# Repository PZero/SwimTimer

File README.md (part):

# SwimTimer

Automatic lap times in the pool: a tag under the swim cap and a poolside display detect start and finish, with no buttons.

Updated on **2026-11-12**. Single public repository `PZero/SwimTimer`: XIAO test tags and their firmware, tools page (GitHub Pages: https://pzero.github.io/SwimTimer/), online collaboration app (Firebase, Italian and English: https://swimtimer-pzero.web.app, with contact form and poolside display demo), ESP32 prototype, nRF52840 tag (KiCad, Gerber, JLCPCB and NextPCB files), programmer HAT, technical wallpapers and three videos (first pool test, progress update and first presentation).

> **Language.** This README is in English. Internal working documents in [`docs/`](docs/) (state, decisions, requirements, design) are written in Italian.

### Houston, we have a problem (3 minutes, latest)

Watch the English version on YouTube: **https://youtu.be/mj6OTWkjgwk**. Italian version: https://youtu.be/85RNvPnFV1E.

The tag stopped in the pool on 11 November 2026: a "black box" diagnosis after every connection showed that the Bluetooth task's stack was too small. The video shows the three changes (black box, bigger stack, poolside station that confirms every block only after saving and reading it back: almost 1,000 blocks on the bench, zero lost) and the stroke-rhythm idea for timing the finish, a promising lead still being checked. Animations drawn in code with made-up data. Sources in [`media/video/`](media/video/) (`genera_video_v4.py`, `musica_v4.py`, `STORYBOARD_v4.md`); the video files are not in the repository.

### The first pool test (2.5 minutes)

Watch the English version on YouTube: **https://youtu.be/bs7WDUuwb-A**. Italian version: https://youtu.be/J01CR2nldp8.

The first real pool test (9 November 2026): IMU filters on the raw data, why the hand-made labels were not precise enough, OpenCV on the underwater video as the new reference, and the decision for a structured method with a small neural network only for the finish. Real images and data from the author's own session (author's choice). Sources in [`media/video/`](media/video/) (`genera_video_v3.py`, `musica_v3.py`); the video files and thumbnails are not in the repository.

### Progress update video (2 minutes)

Watch the English version on YouTube: **https://youtu.be/JLs5JJG4JG8**. Italian version: https://youtu.be/_Htx2DawnF8.

A progress update on the project as of 2026-11-08. The soundtrack is original music generated by code. Sources in [`media/video/`](media/video/); the video files are not in the repository.

### First presentation (2 minutes)

English: **https://youtu.be/EVrdSybpnE4**. Italian: https://youtu.be/_2UzpOqblVI.

## Table of contents
- [What is SwimTimer](#what-is-swimtimer)
- [Current status](#current-status)
- [Test methodology: raw data, video and hand annotation](#test-methodology-raw-data-video-and-hand-annotation)
- [System architecture](#system-architecture)
- [ESP32 prototype, firmware 0.4.3](#esp32-prototype-firmware-043)
- [nRF52840 tag](#nrf52840-tag)
- [XIAO nRF52840 Sense test tags](#xiao-nrf52840-sense-test-tags)
- [Tag to display synchronization](#tag-to-display-synchronization)
- [USB receiver and host (bench results)](#usb-receiver-and-host-bench-results)
- [Base station (Raspberry Pi 3)](#base-station-raspberry-pi-3)
- [Tools page (`tools/index.html`)](#tools-page-toolsindexhtml)
- [Analysis: video (OpenCV) and IMU test bench](#analysis-video-opencv-and-imu-test-bench)
- [Online collaboration app](#online-collaboration-app)
- [External reviews](#external-reviews-v04)
- [Programmer HAT for Raspberry Pi 3/4](#programmer-hat-for-raspberry-pi-34)
- [Poolside display mockup and proposed architecture](#poolside-display-mockup-and-proposed-architecture)
- [Planned features and ideas](#planned-features-and-ideas)
- [Technical wallpaper gallery](#technical-wallpaper-gallery)
- [Repository structure](#repository-structure)
- [How to regenerate the files](#how-to-regenerate-the-files)
- [Ordering flow: JLCPCB and NextPCB](#ordering-flow-jlcpcb-and-nextpcb)
- [Roadmap and open issues](#roadmap-and-open-issues)
- [Privacy and security](#privacy-and-security)
- [License and author](#license-and-author)

## What is SwimTimer

**Problem.** In the pool, lap times and rests get lost. Looking at a watch or pressing a button interrupts the workout.

**Solution.** A small tag with an inertial sensor (accelerometer and gyroscope) is worn under the swim cap. It detects the wall push-off (start), the turns and the stillness at the finish on its own. A poolside display shows the times.

**Physical constraint.** 2.4 GHz BLE does not travel through water. Time is not measured with the radio signal: the sensor on the tag decides. BLE is used only out of the water, to detect proximity to the display and to transfer data. Full feasibility analysis: [`docs/IDEA.md`](docs/IDEA.md) (in Italian).

## Current status

| Area | Status |
|---|---|
| ESP32-S3 + BMI160 prototype, firmware **0.4.3** | Working on the bench; no pool tests yet. Its tools were removed from the tools page on 2026-11-08 |
| LilyGO T-RGB display (4-hand pace clock) | Board works, **screen broken** (torn ribbon cable). Replacement 2.8″ screen to order. Used now without a screen (see the display firmware row) |
| nRF52840 tag **v0.5 "economy"** | Ready: 21.59 x 28.0 mm, 2 layers, DRC 0, ERC 0 errors, `verifica_v05.py` 100/100 pins. JLCPCB files plus NextPCB files (single board and 3x1 / 2x1 panels); JLC placement preview checked, Q1 and U6 rotations fixed (commit `dea9744`) |
| nRF52840 tag **v0.6 "Rev0"** (new) | 4 layers 0.8 mm, 21.59 x 28.5 mm, no BGA (NextPCB Rev0 rejects pitch below 0.45 mm). Files generated; JLC rotations of the new SOT-23 parts still to verify in a JLC preview |
| XIAO nRF52840 Sense test tags | One board in use on the bench ([`hardware/xiao/README.md`](hardware/xiao/README.md)). Firmware 0.5.2 (no automatic sleep on USB power), 0.5.3 (USB during a recording closes it and restarts in normal mode) and 0.5.4 (charge current 100 mA) flashed and checked on the bench; test cell 1000 mAh; pool recording download and recorded data not yet checked; not yet used in the pool |
| XIAO firmware **0.6.1** (`firmware/xiao-stream`, test build on both tags) | Automatic resume after a crash or watchdog reset (max 3 in a row), 8 s watchdog, fault context and persistent diary, IMU FIFO realignment with content check, continuous session time (start-up 500 ms), no idle without USB, USB rules, standby command from the display. Standby from the page, rest stop and idle on the charger **not yet verified**. The published OTA release is still 0.5.4 |
| Tag firmware **0.6.3** (`firmware/xiao-stream`) | 238-byte fragments (READY v2), notification queue, 2M PHY / DLE, DIAGNOSIS message after every connection, 4-aligned flash reads, BLE stack 8 KB. **0.6.4** (stack 10 KB, stays connected while recording, DIAGNOSIS2; written 2026-11-12, 60-minute bench run pending) |
| Receiver firmware **0.1.6** (`firmware/ricevitore`) + host `stazione/ricevitore_host.py` | XIAO nRF52840 Sense on USB, central for 2 tags; the host saves, fsyncs and re-reads each block before the OK. Bench: 1 tag ~16.5 KB/s, 2 tags ~17.6 KB/s total, 0 blocks lost. Receiver **0.1.7** written (DIAGNOSIS2 relay). Runs as a service on the Raspberry Pi 3 (2 tags downloaded, 0 blocks discarded); not yet tested in the pool |
| Display firmware `firmware/display-sync` | LilyGO T-RGB without a working screen: receives the blocks from up to 3 tags, verifies, writes to microSD and confirms. Creates the Wi-Fi network «SwimTimer» with a status page for iPhone (`http://192.168.4.1`), which also shows warnings, the recording button and the standby button for the tags. Dry run (0.6.0): 2 tags x 15 min, 666 blocks saved and confirmed, 0 CRC errors, 0 anomalies. Signal strength still to be tuned |
| Display enclosure `hardware/display-involucro/` | Parametric OpenSCAD design: PLA vase, silicone cap, fork with a 15° detent swivel; STL files and renders. Fit on the real board still to be checked |
| Tools page `tools/index.html` | XIAO only: Live, Recording, Annotation and Firmware tabs, USB / Bluetooth / Demo. Also published on the Firebase site at `/strumenti/`, with an "Upload online" button. Tested in the browser with Demo and simulated ports, not yet with the real XIAO over USB for a full download |
| Online collaboration app | Bilingual (IT/EN) public landing page with a contact form, and members' area (Google login, admin approval of new accounts, admin page for messages). Poolside display section with a live demo. Firestore rules tested with 17 emulator tests. Not yet used with real sessions |
| Test campaign 1 | **Planned**: one swimmer (the author), 50 m pool, wall drills, then a real training session as verification. See [Test methodology](#test-methodology-raw-data-video-and-hand-annotation) |
| Order | **Not placed yet**: preview, finish choice (HASL/ENIG), DFM ticket and cost decision pending |
| nRF52840 tag firmware | To be written (Zephyr / nRF Connect SDK) |
| Programmer HAT for Raspberry Pi 3/4 | Designed, regenerated on v0.5 (TP1-TP7 unchanged), DRC 0; **not built yet** |

## Test methodology: raw data, video and hand annotation

The core of SwimTimer is a set of **filters** that recognise strokes, breaths, turns, starts and finishes from the IMU of a tag worn under the cap. Before writing those filters we need **ground truth**: real swimming data in which every event is known. For this phase the tag is a **Seeed XIAO nRF52840 Sense** (same SoC as the custom board, which is still being manufactured) running the pool recording firmware [`firmware/xiao-stream`](firmware/xiao-stream/) 0.5.x.

**Test campaign 1 (planned).** The first campaign has a deliberately small scope:

- **One swimmer only**: the author of the project. No other person is recorded.
- **Pool**: 50 m, with a wall for the drills.
- **Drills at one wall** (turns, starts, finishes), repeated to collect many examples of each event with known timing.
- **Real training** afterwards, used to verify the filters on a session that was not used to tune them.
- **Video** from an iPhone and an Insta360 camera, both at 30 fps for now (the page does not yet handle 25 fps).
- **Annotation by hand first**, in the *Annotation* tab. Filters are developed and compared **only in the web page**, after the whole session is annotated.

The steps below describe the procedure of each session.

1. **Record raw data in the pool.** The swimmer wakes the tag (2 taps, blue LED, 2 taps): it records the raw accelerometer and gyroscope at 208 Hz to its flash, with BLE off (BLE does not cross water). The swimmer is filmed from the deck with a phone (H.264, 30 fps).
2. **Sync gesture.** With the tag under the cap, the swimmer gives **5 large, clearly visible taps** on it. The taps are sharp peaks in the data and visible frames in the video: the **5th tap** is the common reference point.
3. **Swim 5-10 minutes,** then put the tag in the bag: after 180 s of rest it closes the recording and sleeps. The data survives even if the battery runs out on the way home.
4. **Download at home over USB** from the *Recording* tab of [`tools/index.html`](tools/index.html) (Web Serial) or with [`scarica.py`](firmware/xiao-stream/scarica.py): a `.swr` file.
5. **Align video and data** in the *Annotation* tab: press **X** on the video frame of the 5th tap and click the 5th peak in the zoomable raw-data chart. The page computes the offset; from then on the data follow the video, forwards and backwards.
6. **Annotate events by hand** while watching the video (slow motion, frame by frame): **B** stroke (hand entry), **R** breath (mouth out of the water), **V** turn start, **F** turn end, **P** start, **A** arrival. Events are stored in video time, so a later offset correction moves them all at once; they are saved as a project JSON and a CSV.
7. **Develop the filters** on the raw data, re-process the same recording and **compare** the automatic events with the hand-annotated ones (matches within a time tolerance, precision, recall, timing error). This happens only after the whole session has been annotated.

Recordings, videos and annotation projects are health data: they stay on the PC and are excluded from git; the repository only contains code and invented test data.

## System architecture

```mermaid
flowchart LR
  subgraph TAG[Tag under the swim cap]
    IMU[6-axis IMU] -- SPI --> MCU[nRF52840 / ESP32-S3<br/>BLE]
    FL[Flash] -- SPI --> MCU
    CEL[LiPo cell] --> MCU
  end
  MCU -- "BLE advertising (out of the water)" --> DSP[Poolside display<br/>LilyGO T-RGB 2.8 inch]
  MCU -- "GATT / OTA (out of the water)" --> WEB[Analysis page<br/>Web Bluetooth]
  MCU -. "flash recording,<br/>downloaded later" .-> WEB
  WEB -. "downloaded .swr files" .-> PCU[Member's browser]
  PCU -. "upload in chunks, annotations" .-> APP[Online collaboration app<br/>Firebase Spark, Firestore]
  DSP -- "pace clock, times" --> SWI[Swimmer]
  CHG[Charging base / programmer] -- "contacts under the tag" --> TAG
```

### Target poolside chain (decided 2026-11-12)

```text
Tag (XIAO nRF52840, under the cap)
   |  BLE, out of the water (encrypted sync protocol)
   v
Receiver (XIAO nRF52840 Sense, USB; firmware/ricevitore)
   |  USB serial, CRC frames
   v
Host (stazione/ricevitore_host.py, --stato JSON) on Raspberry Pi 3 (Raspberry Pi OS Lite 64-bit, headless)
   |  pannello.py (HTTP :8080) + pannello.html, kiosk browser on HDMI
   v
Portable 15.6" HDMI monitor (poolside display)
```

The receiver, the host and the Raspberry Pi station (systemd services, status panel, kiosk) are implemented; the Pi boots straight into the panel. See [USB receiver and host](#usb-receiver-and-host-bench-results).

Tests run with two tags streaming raw data; in normal operation only events (start, turns, stop) are exchanged. The LilyGO T-RGB display remains a test device for synchronization.

- **Synchronization.** After the swim the tag pushes its recorded blocks to the poolside display over BLE; the display verifies, stores and confirms them. See [Tag to display synchronization](#tag-to-display-synchronization).
- **Tag.** Under the cap, pressed against the skull. It decides START, turns and STOP on its own using the IMU and logs raw data to flash.
- **Poolside display.** Receives the tag's BLE advertisements without connecting. Shows a 4-hand pace clock. Goes to sleep after 5 minutes without a tag.
- **Tools page.** [`tools/index.html`](tools/index.html) connects to the XIAO over USB or Bluetooth, downloads and annotates recordings and updates the firmware. Details in [Tools page](#tools-page-toolsindexhtml).
- **Online app.** Optional collaboration area for sessions, video links and annotations. Details in [Online collaboration app](#online-collaboration-app).
- **BLE out of the water.** Underwater the signal disappears within a few centimetres: during the swim the tag works alone and hands over its data when the swimmer emerges or at the end of the session.

## ESP32 prototype, firmware 0.4.3

The prototype was used to tune the algorithms before the XIAO and custom boards. Since 2026-11-08 the tools page no longer supports it.

**Tag (prototype).** ESP32-S3 SuperMini + BMI160 (GY-BMI160), LiPo with main switch. Bill of materials: [`hardware/bom.md`](hardware/bom.md). Wiring: [`hardware/schema.md`](hardware/schema.md) (both in Italian).

**Firmware 0.4.3** (`firmware/test-collegamenti`, arduino-cli, core `esp32:esp32` 3.3.12):
- +/-16 g and 100 Hz, set with the sensors on and read back (up to 5 attempts);
- flash with two program copies and about 1.9 MB of LittleFS (about 40 minutes at 50 Hz);
- double tap = start recording, triple tap = stop (software detection, unreliable: about 1 in 10);
- BLE with data, status, commands, OTA and version; the same commands over USB; Bluetooth update with automatic rollback to the previous version;
- automatic I2C bus recovery, RGB LED feedback, last reset reason, voltage dividers on GPIO 1 (battery) and GPIO 2 (5V pin).

**Display** (`firmware/display-prova`): LilyGO T-RGB 2.8 inch, PlatformIO with espressif32 6.9.0, driver copied and adapted in `src/trgb/` (MIT license, Xinyuan-LilyGO).

**Build and upload the tag firmware:**
```
arduino-cli compile --fqbn esp32:esp32:esp32s3:CDCOnBoot=cdc --upload -p <COM> firmware/test-collegamenti
```

Related documents (in Italian): [`docs/RICERCA-ALGORITMI.md`](docs/RICERCA-ALGORITMI.md) (algorithm research), [`docs/LEZIONI-APPRESE.md`](docs/LEZIONI-APPRESE.md) (13 prototype lessons for the miniaturised board), [`docs/REQUISITI.md`](docs/REQUISITI.md) (requirements), [`docs/DESIGN.md`](docs/DESIGN.md) (design).

## nRF52840 tag

**Goal.** Replace the prototype with a miniature tag for the swim cap, assembled by the fab, with contact charging and programming through pads on the underside. Design document: [`hardware/nrf52840/progetto.md`](hardware/nrf52840/progetto.md) (Italian).

### Version history

| Version | Date | Board | Content | Outcome |
|---|---|---|---|---|
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
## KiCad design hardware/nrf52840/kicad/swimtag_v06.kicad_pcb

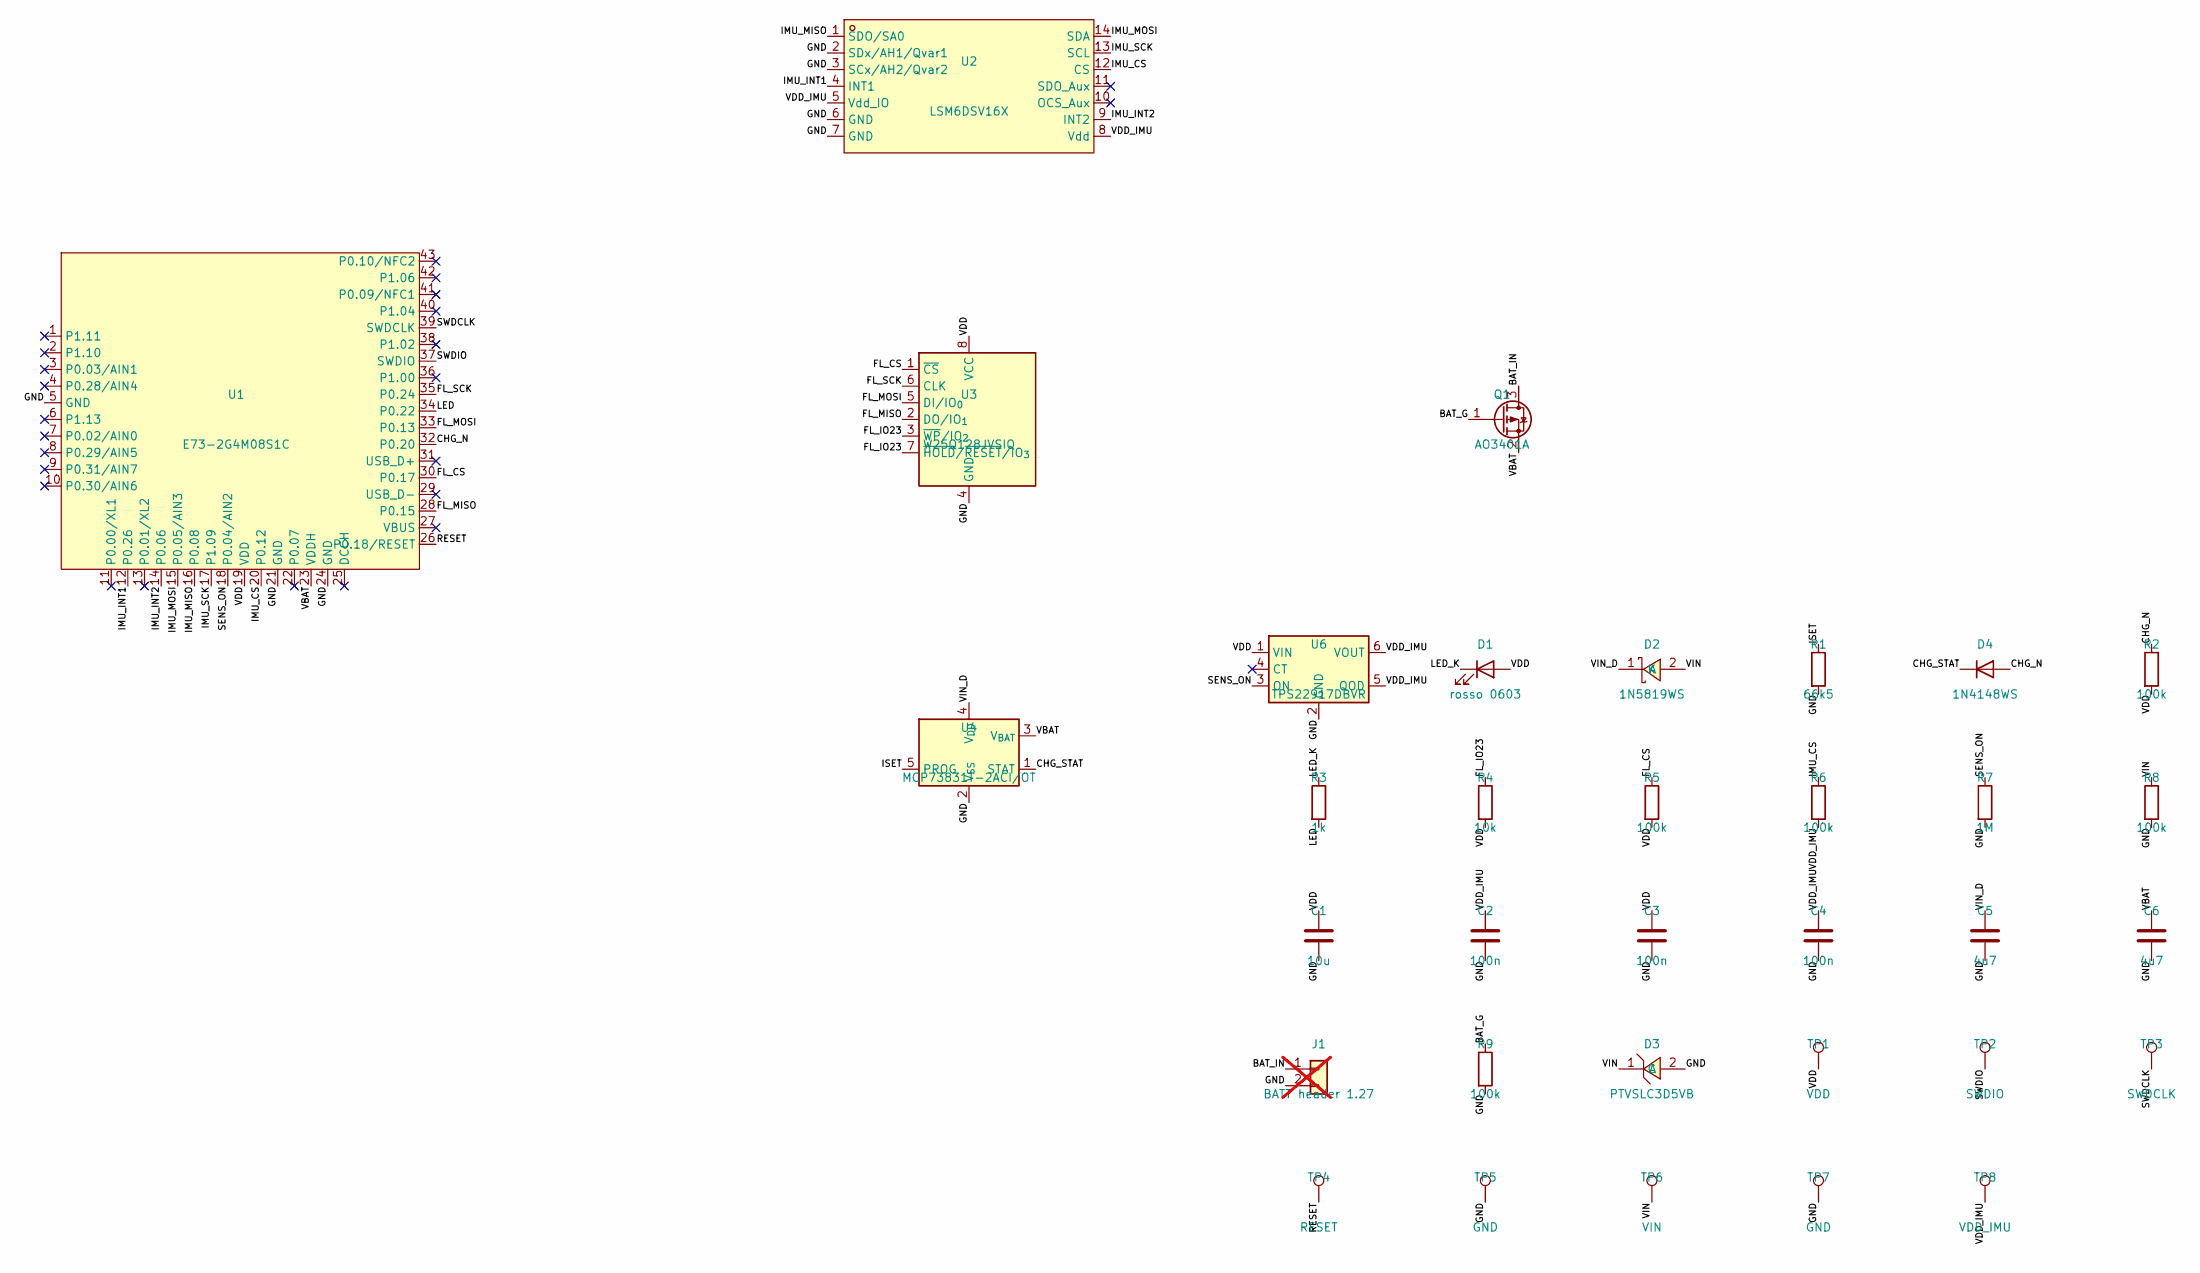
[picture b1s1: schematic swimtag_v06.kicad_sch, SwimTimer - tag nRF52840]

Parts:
C1: 10u; C_0402_1005Metric; LCSC C15525
C2, C3, C4: 100n; C_0402_1005Metric; LCSC C1525
C5, C6: 4u7; C_0402_1005Metric; LCSC C23733
D1: rosso 0603; LED_0603_1608Metric; LCSC C2286
D2: 1N5819WS; SOD-323_L1.8-W1.3-LS2.5-RD; LCSC C191023
D3: PTVSLC3D5VB; SOD-323_L1.8-W1.3-LS2.5-RD; LCSC C41408025
D4: 1N4148WS; SOD-323_L1.8-W1.3-LS2.5-RD; LCSC C2128
J1: BATT header 1.27; HDR-SMD_2P-P1.27-V-M-LS4.2-R1; LCSC C55213900; not fitted
Q1: AO3401A; SOT-23; LCSC C15127
R1: 66k5; R_0402_1005Metric; LCSC C172114
R2, R5, R6, R8, R9: 100k; R_0402_1005Metric; LCSC C25741
R3: 1k; R_0402_1005Metric; LCSC C11702
R4: 10k; R_0402_1005Metric; LCSC C25744
R7: 1M; R_0402_1005Metric; LCSC C26083
TP1: VDD; TestPoint_Pad_D2.0mm_NoCY
TP2: SWDIO; TestPoint_Pad_D2.0mm_NoCY
TP3: SWDCLK; TestPoint_Pad_D2.0mm_NoCY
TP4: RESET; TestPoint_Pad_D2.0mm_NoCY
TP5: GND; TestPoint_Pad_D2.0mm_NoCY
TP6: VIN; TestPoint_Pad_D2.5mm
TP7: GND; TestPoint_Pad_D2.5mm
TP8: VDD_IMU; TestPoint_Pad_D0.8mm
U1: E73-2G4M08S1C; WIRELM-SMD_E73-2G4M08S1C; LCSC C356849
U2: LSM6DSV16X; LGA-14_L3.0-W2.5-P0.50-BR; LCSC C5267406
U3: W25Q128JVSIQ; SOIC-8_5.3x5.3mm_P1.27mm; LCSC C97521
U4: MCP73831T-2ACI/OT; SOT-23-5; LCSC C424093
U6: TPS22917DBVR; SOT-23-6; LCSC C2681320

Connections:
/BAT_G: Q1.1 (G), R9.1
/BAT_IN: J1.1, Q1.3 (D)
/CHG_N: D4.2 (A), R2.1, U1.32 (P0.20)
/CHG_STAT: D4.1 (K), U4.1 (STAT)
/FL_CS: R5.1, U1.30 (P0.17), U3.1 (~CS)
/FL_IO23: R4.1, U3.3 (~WP/IO_{2}), U3.7 (~HOLD/~RESET/IO_{3})
/FL_MISO: U1.28 (P0.15), U3.2 (DO/IO_{1})
/FL_MOSI: U1.33 (P0.13), U3.5 (DI/IO_{0})
/FL_SCK: U1.35 (P0.24), U3.6 (CLK)
/GND: C1.2, C2.2, C3.2, C4.2, C5.2, C6.2, D3.2 (A), J1.2, R1.2, R7.2, R8.2, R9.2, TP5.1, TP7.1, U1.5 (GND), U1.21 (GND), U1.24 (GND), U2.2 (SDx/AH1/Qvar1), U2.3 (SCx/AH2/Qvar2), U2.6 (GND), U2.7 (GND), U3.4 (GND), U4.2 (V_{SS}), U6.2 (GND)
/IMU_CS: R6.1, U1.20 (P0.12), U2.12 (CS)
/IMU_INT1: U1.12 (P0.26), U2.4 (INT1)
/IMU_INT2: U1.14 (P0.06), U2.9 (INT2)
/IMU_MISO: U1.16 (P0.08), U2.1 (SDO/SA0)
/IMU_MOSI: U1.15 (P0.05/AIN3), U2.14 (SDA)
/IMU_SCK: U1.17 (P1.09), U2.13 (SCL)
/ISET: R1.1, U4.5 (PROG)
/LED: R3.2, U1.34 (P0.22)
/LED_K: D1.1 (K), R3.1
/RESET: TP4.1, U1.26 (P0.18/RESET)
/SENS_ON: R7.1, U1.18 (P0.04/AIN2), U6.3 (ON)
/SWDCLK: TP3.1, U1.39 (SWDCLK)
/SWDIO: TP2.1, U1.37 (SWDIO)
/VBAT: C6.1, Q1.2 (S), U1.23 (VDDH), U4.3 (V_{BAT})
/VDD: C1.1, C3.1, D1.2 (A), R2.2, R4.2, R5.2, TP1.1, U1.19 (VDD), U3.8 (VCC), U6.1 (VIN)
/VDD_IMU: C2.1, C4.1, R6.2, TP8.1, U2.5 (Vdd_IO), U2.8 (Vdd), U6.5 (QOD), U6.6 (VOUT)
/VIN: D2.2 (A), D3.1 (C), R8.1, TP6.1
/VIN_D: C5.1, D2.1 (K), U4.4 (V_{DD})

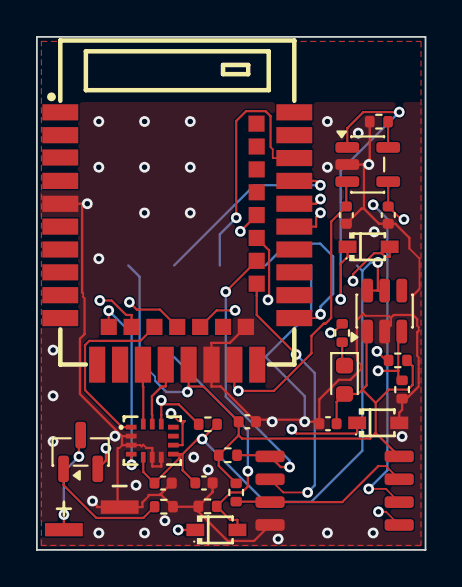
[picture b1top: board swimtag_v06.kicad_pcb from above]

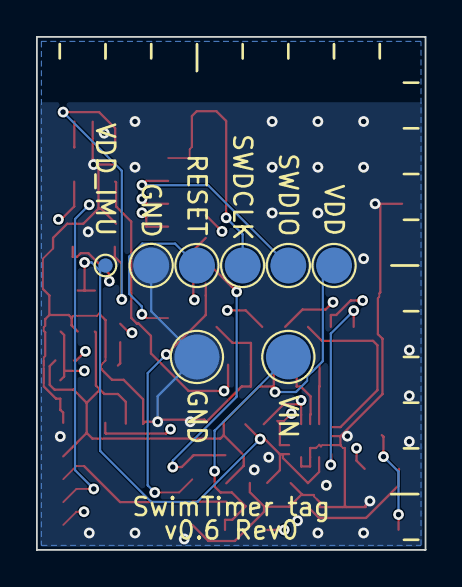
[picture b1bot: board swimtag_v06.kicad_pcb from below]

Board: 4 copper layers, 21.6 x 28.5 mm, 34 parts (8 on the bottom side), 28 nets.

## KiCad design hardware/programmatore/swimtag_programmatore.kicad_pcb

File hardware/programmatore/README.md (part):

# Adattatore di programmazione e collaudo (pogo jig, forma di HAT) per il tag SwimTimer v0.5

Basetta a una faccia, a foro passante, da realizzare a mano con il **toner transfer**, con **forma e fori di un HAT del Raspberry Pi** (65 x 56,5 mm, angoli r = 3 mm, 4 fori M2,5 a 58 x 49 mm). Si **innesta direttamente sul connettore a 40 pin** del Pi 3 o 4 (header femmina 2x20 completo, niente cavetti); sulla faccia superiore 7 molle (pogo pin) cadono sulle piazzole sotto il tag: 5 di debug SWD (VDD, SWDIO, SWCLK, RESET, GND) e 2 di ricarica (VIN, GND). Il Pi programma con OpenOCD in bit-bang sui GPIO e puo' anche **ricaricare la cella** del tag mentre e' collegato.

> **MAI il 3,3 V del Raspberry Pi sul VDD del tag.** Il tag si alimenta dalla sua cella; la piazzola VDD (pin J4 dell'adattatore) serve solo al tester e non e' collegata al connettore. Sul connettore sono collegati **solo** i pin 2 (5 V, attraverso PTC e ponticello), 12, 18, 20 (GND) e 22; gli altri 35 restano scollegati. Al primo avvio il VDD del tag e' 1,8 V (UICR vuoto), dopo `UICR.REGOUT0` e un reset 3,3 V.

Documento completo (schema, distinta, stampe 1:1, procedura illustrata, innesto, OpenOCD, problemi): **[`Programmatore_SwimTag_v0.5.pdf`](Programmatore_SwimTag_v0.5.pdf)**. Le **stampe 1:1 sono alle pagine 6 (rame speculare, 8 copie), 7 (posizioni componenti), 8 (ingrandimento 2:1 con tutte le etichette) e 9 (mappa fori)**; gli stessi fogli sono anche in [`stampa/`](stampa/).

## File

| File | Contenuto |
|---|---|
| `modello.py` | geometria: legge `TP1-TP7` e il contorno dal PCB del tag e ricava HAT, pogo, battute, appoggi, piste |
| `genera_kicad.py` | scrive `swimtag_programmatore.kicad_pcb/.kicad_sch/.kicad_pro`; con `--drc` esegue DRC ed ERC con `kicad-cli` |
| `genera_pdf.py`, `pdfbase.py` | PDF unico e fogli di stampa (PyMuPDF) |
| `swimtag_programmatore.*` | progetto KiCad (schema + PCB): piste 0,8 mm, distanze >= 0,5 mm, piazzole >= 2,0 mm, una sola faccia di rame (F.Cu) |
| `stampa/rame_speculare_1a1.pdf`, `stampa/componenti_1a1.pdf` | fogli 1:1 |
| `bom.md` | distinta con prezzi e link |
| `img/` | render KiCad usati nel PDF |

**Risultato di `python genera_kicad.py --drc`: DRC 0 violazioni, 0 pad non collegati, ERC 0** (kicad-cli 10.0.6; il controllo e' sensibile: con distanza 0,6 mm il DRC segnala errori).

## Rigenerare dopo la ricompattazione della scheda

```
cd hardware/programmatore
python genera_kicad.py --drc     # rilegge TP1-TP7 e Edge.Cuts da ../nrf52840/kicad/swimtag_economica.kicad_pcb
python genera_pdf.py             # PDF e fogli di stampa (pip install pymupdf; per i render serve kicad-cli)
# altro file del tag:  SWIMTAG_PCB=percorso/file.kicad_pcb python genera_kicad.py
```

Il tag viene solo traslato nell'HAT (angolo in alto a sinistra a u = 22,5, v = 24,0 mm, costanti `OU`, `OV`): pogo e battute seguono le sue piazzole e i suoi bordi. Fisso nello script: la fila SWD a 2,54 mm e i contatti di ricarica sotto SWDIO e RESET (lo sbroglio dei ponti dipende da questo; lo script avvisa se cambia). Costanti in `modello.py`: `FORO_POGO` (1,5 mm), `LARG_PISTA`, `ALT_BATTUTE` (2,5 mm), `GIOCO_BATTUTA` (0,1 mm). Il PCB del tag e' **solo letto**; dopo la ricompattazione rigenerare e ristampare.

## Forma di HAT e innesto

- Connettore al centro tra i fori, a 3,5 mm dal bordo lungo (specifica HAT ufficiale: **verificare sul proprio Pi** prima di forare: un errore si vede subito perche' i fori M2,5 non coincidono). Pin 1 sul lato della scheda SD, evidenziato da un "1" inciso nel rame; "USB->" inciso verso le porte USB/Ethernet (che l'HAT da 65 mm lascia scoperte).
- **Header femmina 2x20 completo**: montato **da sotto**, saldato **sopra**. Le **code dei pin dispari (fila interna) si tagliano** prima di montarlo (cosi' la fila interna non ha fori e le piste dei 5 pin usati, tutti sulla fila esterna, escono liberamente); le 20 code della fila esterna si saldano (ritenzione) e solo 5 sono collegate.
- Distanziali M2,5 femmina-femmina da **11 mm** (header femmina 8,5 mm + 2,5 mm di plastica del maschio del Pi) ai 4 fori; poggiano sul Pi e non serve fissarli: sostengono anche la pressione quando si preme il tag.
- Sotto l'HAT: solo il connettore (8,5 mm), i corpi degli header maschio (2,5 mm) e le code tagliate.
- **Rame sopra** (come un HAT vero), quindi stampa **speculare** e tutto si salda dal lato in cui si vedono le piste (resistenze, LED e PTC con il corpo sollevato 1-2 mm; header maschio inseriti da sotto con il pin lungo in alto).

### E se fosse innestato ruotato di 180 gradi?
L'HAT sporgerebbe di 49 mm oltre il bordo del Pi e solo due distanziali cadrebbero sui fori. Se lo si forzasse: la presa "pin 2k" finisce sul pin 41-2k del Pi, e i pin pari del Pi (5 V, GND, GPIO) incontrano la fila interna con le code tagliate (nessun contatto). Risultato:

| Presa dell'HAT | Pin del Pi | Effetto |
|---|---|---|
| pin 2 (5 V, verso PTC) | 39 = GND | la linea 5 V va a massa: nessun danno (il tag vede 0 V con JP1 1-2) |
| pin 12 (RESET) | 29 = GPIO5 | GPIO libero |
| pin 18 (SWDIO) | 23 = GPIO11 | GPIO libero |
| pin 20 (GND adattatore) | 21 = GPIO9 | massa del tag/alimentatore esterno su un GPIO in ingresso: nessun corto |
| pin 22 (SWCLK) | 19 = GPIO10 | GPIO libero |
| prese flottanti | 1 e 17 (3,3 V) | cadono su rame isolato |

**Nessun caso pericoloso**: i 3,3 V e i 5 V del Pi non toccano mai una linea collegata del tag, ne' innestato giusto ne' ruotato (il 5 V passa solo dal pin 2 e da JP1, spento di default). Nessuna protezione aggiuntiva necessaria oltre a PTC e alle 1 kohm.

## Pogo e centraggio

- **Pogo P75-E2** (testa a corona) con **ricettacolo R75-2W** a saldare; alternativa P50/R50 (foro 1,0 mm). Foro del ricettacolo **1,5 mm da verificare con il pezzo** (dati dei venditori discordi), piazzola ovale 2,0 x 3,2 mm (0,54 mm tra piazzole vicine). Corsa ~2-2,5 mm.
- Tag a **faccia in giu'** su 3 blocchetti di plastica da 2,5 mm incollati (S4-S6); punta libera dei pogo a **4,0 mm** (compressione 1,5 mm). Altezza della testa del ricettacolo = 4,0 mm - L (L = quanto la punta sporge a riposo; procedura nel PDF, sezione 7, con sezione quotata).
- **Centraggio:** tre pin di battuta (S1, S2 sul bordo sinistro, S3 sul bordo alto), cioe' i bordi dove ci sono le tacche serigrafiche del tag; gioco 0,1 mm; errore totale stimato ~ +-0,3 mm. Pogo e battute sono sulla parte lontana dal connettore.

## Piedinatura sul connettore

| Pin fisico | GPIO (BCM) | Segnale | Collegamento |
|---|---|---|---|
| 18 | GPIO24 | SWDIO | R1 1 kohm in serie -> P2 |
| 22 | GPIO25 | SWCLK | R2 1 kohm -> P3 |
| 12 | GPIO18 | RESET (P0.18) | R3 1 kohm -> P4 |
| 20 | - | GND | massa comune (anche carica) |
| 2 | - | 5 V solo carica | PTC F1 -> JP1 -> J3 -> P6 |

R2 e R3 sono resistenze "lunghe" (piedini a 10,16 mm) che scavalcano altre piste: sul tag l'ordine e' SWDIO-SWCLK-RESET-GND, sul connettore RESET-SWDIO-GND-SWCLK, quindi su una faccia sola le piste si incrocerebbero. I GPIO sono quelli delle configurazioni OpenOCD storiche (`raspberrypi2-native.cfg`: SWCLK GPIO25, SWDIO GPIO24, SRST GPIO18); le versioni piu' recenti hanno spostato i default (SWCLK GPIO11, SWDIO GPIO8), per questo `swimtag_pi.cfg` assegna i pin esplicitamente.

## Ricarica (in parallelo a SWD)

I pogo P6 (VIN) e P7 (GND) caricano la cella 401012 da 40 mAh tramite il BQ25101 del tag (13,5 mA, terminazione al 10 % = ~1,35 mA, timer 10 h; ~3-3,5 h da vuota).

- **JP1** (header 1x3 + ponticello): **nessun ponticello = ricarica OFF (predefinito)**; 1-2 = 5 V dal Pi (pin 2, via PTC F1); 2-3 = 5 V esterno su J2 (alimentatore limitato a 50-100 mA).
- **LED verde D1 + R4 1 kohm in parallelo** dopo JP1 e prima di J3 (~3 mA, non entra nella misura).
- **J3** (header 1x2): tester in serie in portata mA; senza tester **serve un ponticello**. **F1**: PTC radiale 0,1 A sul 5 V del Pi.
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
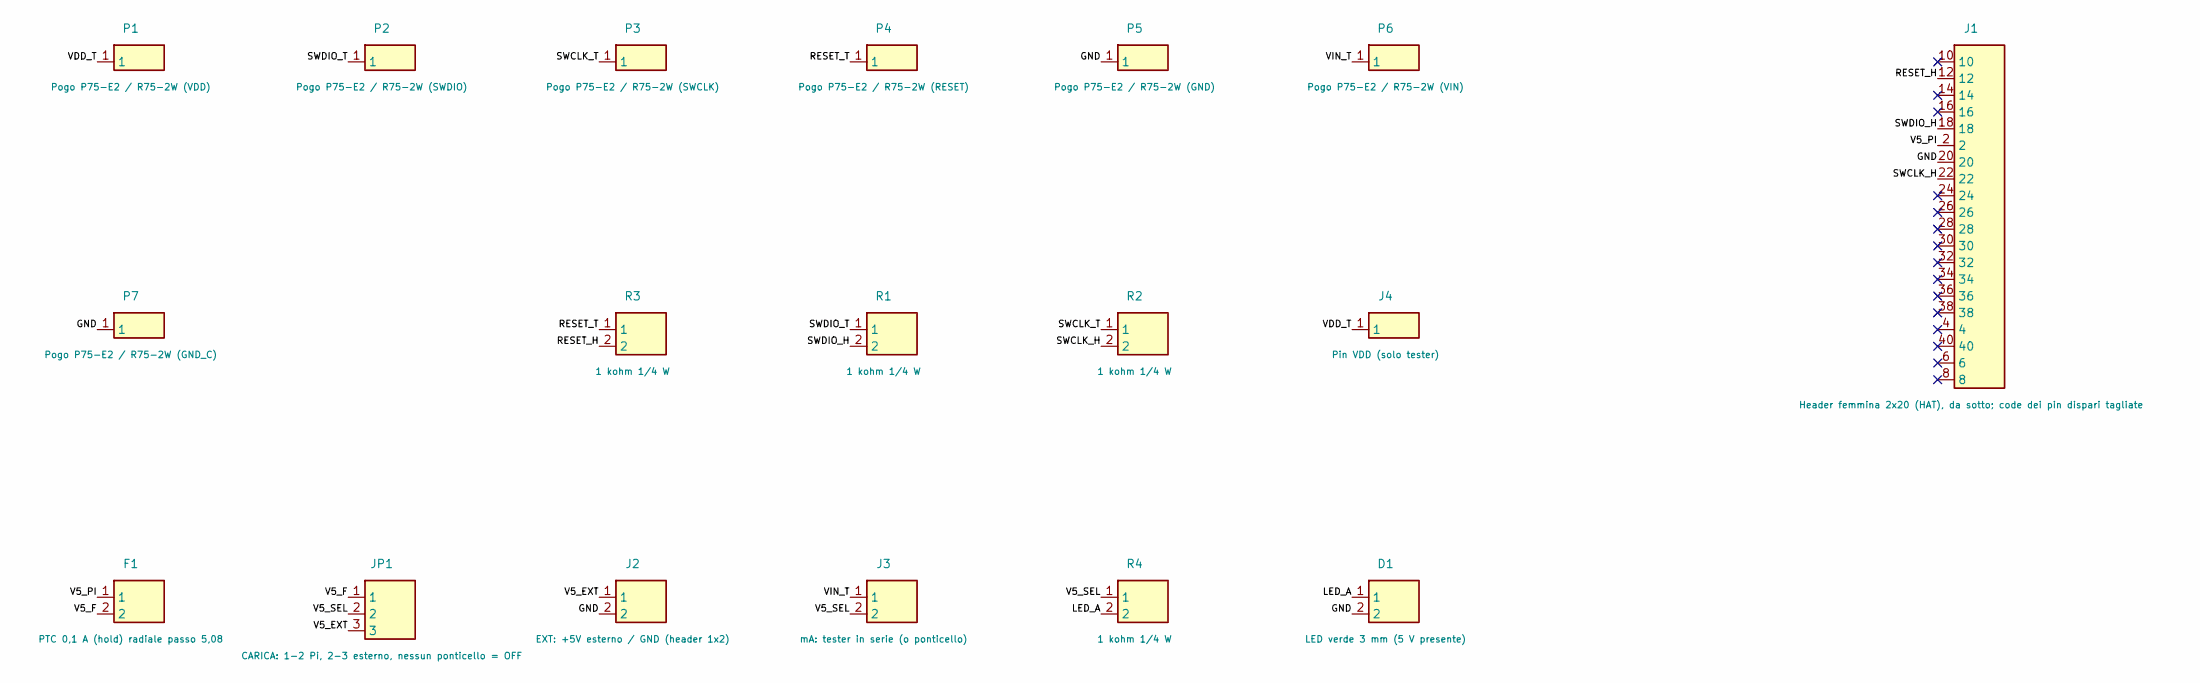
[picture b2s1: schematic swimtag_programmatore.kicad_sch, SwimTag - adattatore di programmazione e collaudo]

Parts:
D1: LED verde 3 mm (5 V presente); LED_P2.54
F1: PTC 0,1 A (hold) radiale passo 5,08; PTC_Radial_P5.08
J1: Header femmina 2x20 (HAT), da sotto; code dei pin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; Header_F_2x20_HAT
J2: EXT: +5V esterno / GND (header 1x2); Header_1x2_P2.54
J3: mA: tester in serie (o ponticello); Header_1x2_P2.54
J4: Pin VDD (solo tester); Header_1x1
JP1: CARICA: 1-2 Pi, 2-3 esterno, nessun ponticello = 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; Header_1x3_P2.54
P1: Pogo P75-E2 / R75-2W (VDD); Pogo_P75_ricettacolo
P2: Pogo P75-E2 / R75-2W (SWDIO); Pogo_P75_ricettacolo
P3: Pogo P75-E2 / R75-2W (SWCLK); Pogo_P75_ricettacolo
P4: Pogo P75-E2 / R75-2W (RESET); Pogo_P75_ricettacolo
P5: Pogo P75-E2 / R75-2W (GND); Pogo_P75_ricettacolo
P6: Pogo P75-E2 / R75-2W (VIN); Pogo_P75_ricettacolo
P7: Pogo P75-E2 / R75-2W (GND_C); Pogo_P75_ricettacolo
R1, R2, R3, R4: 1 kohm 1/4 W; R_1k

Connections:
/GND: D1.2, J1.20, J2.2, P5.1, P7.1
/LED_A: D1.1, R4.2
/RESET_H: J1.12, R3.2
/RESET_T: P4.1, R3.1
/SWCLK_H: J1.22, R2.2
/SWCLK_T: P3.1, R2.1
/SWDIO_H: J1.18, R1.2
/SWDIO_T: P2.1, R1.1
/V5_EXT: J2.1, JP1.3
/V5_F: F1.2, JP1.1
/V5_PI: F1.1, J1.2
/V5_SEL: J3.2, JP1.2, R4.1
/VDD_T: J4.1, P1.1
/VIN_T: J3.1, P6.1

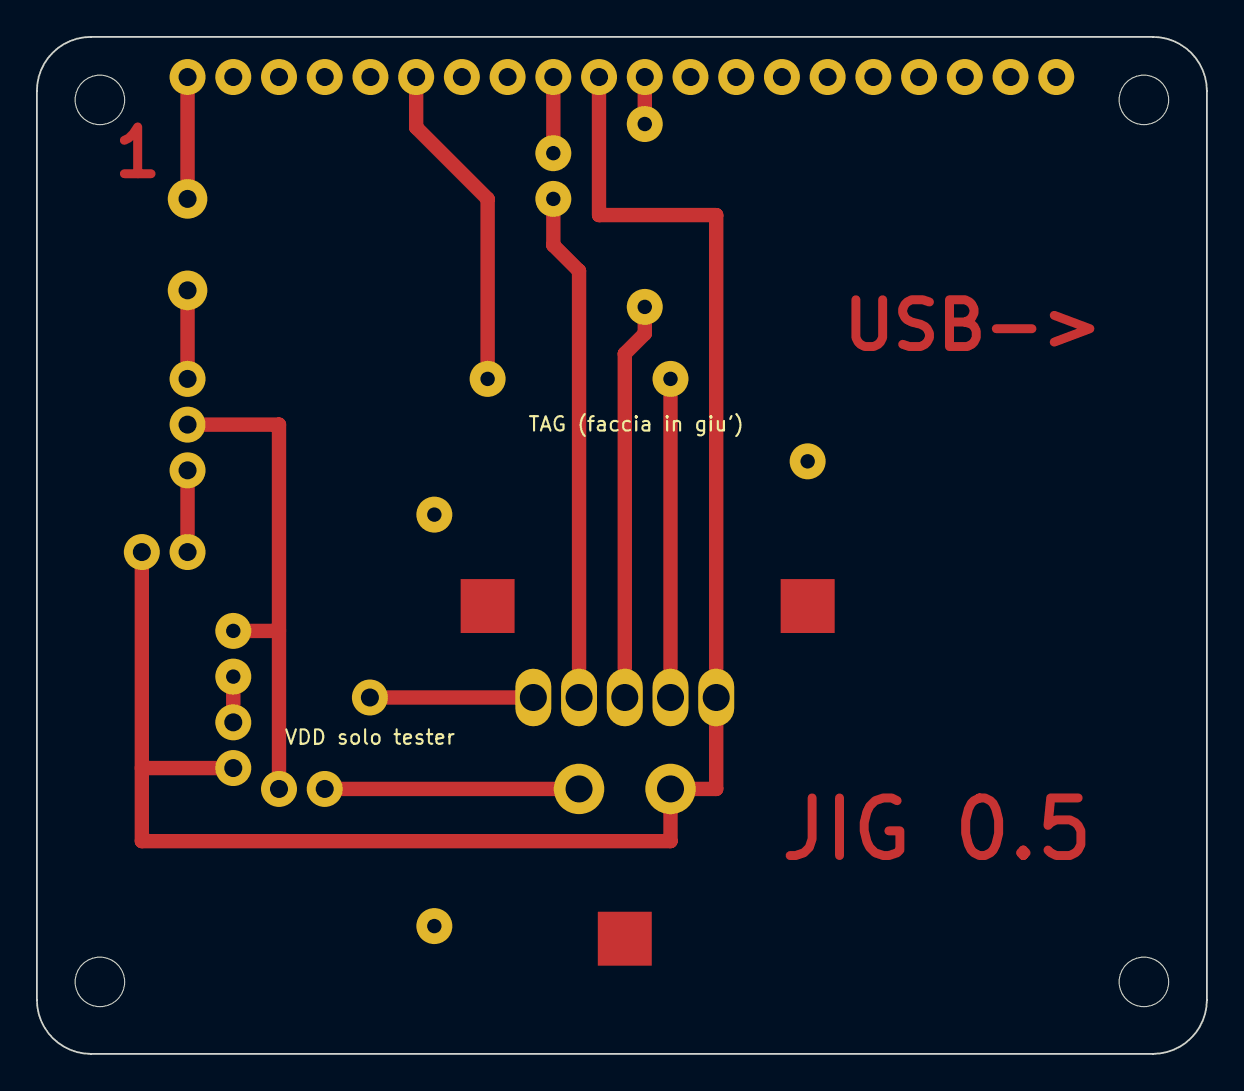
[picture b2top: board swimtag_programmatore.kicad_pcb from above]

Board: 2 copper layers, 65.0 x 56.5 mm, 28 parts (0 on the bottom side), 14 nets.

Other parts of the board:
H1, H2, H3, H4: Foro M2,5 (HAT); MountingHole_M2.5
S1, S2: Battuta lato sinistro (pin 0,64 mm); Header_1x1
S3: Battuta lato alto (pin 0,64 mm); Header_1x1
S4, S5, S6: Sede dell'appoggio (blocchetto 2,5 mm incollato); Glue_3x3

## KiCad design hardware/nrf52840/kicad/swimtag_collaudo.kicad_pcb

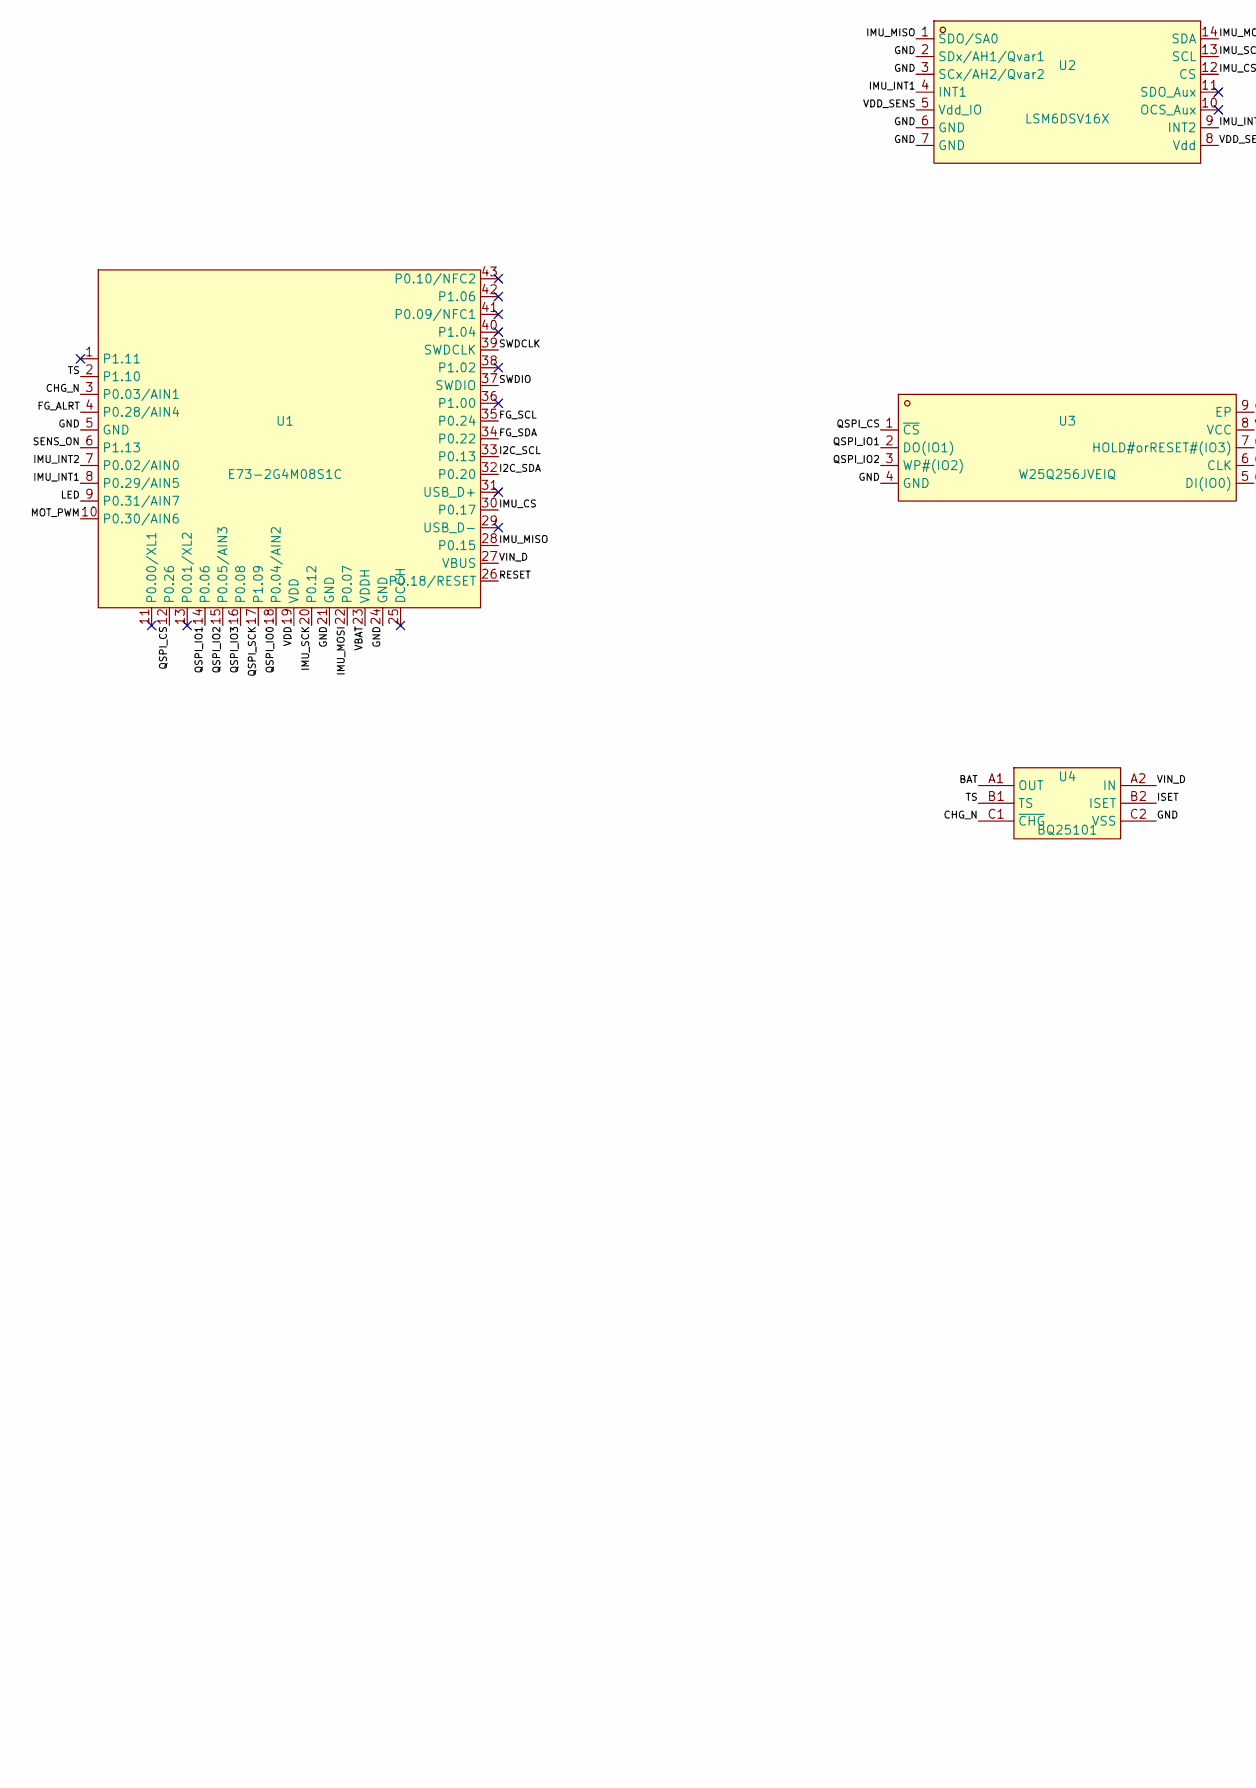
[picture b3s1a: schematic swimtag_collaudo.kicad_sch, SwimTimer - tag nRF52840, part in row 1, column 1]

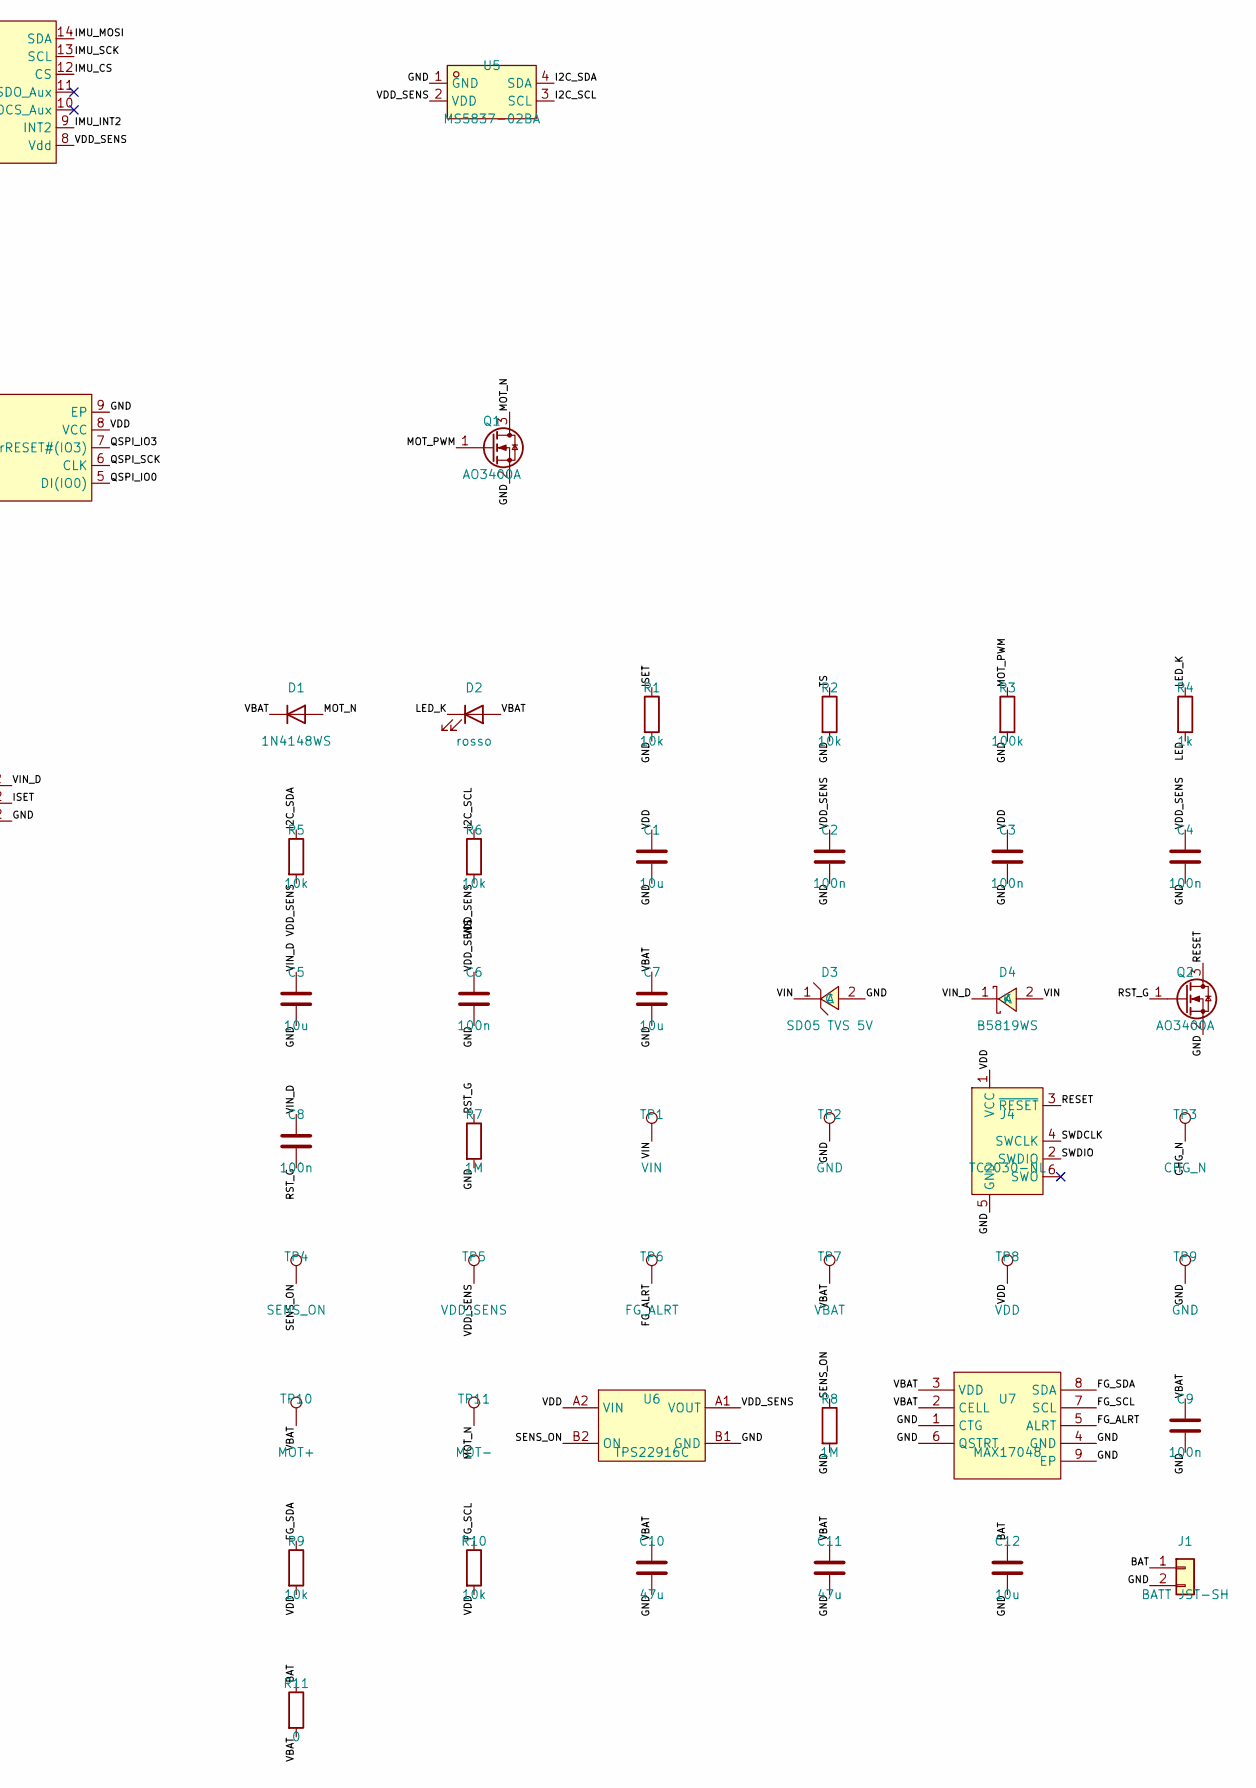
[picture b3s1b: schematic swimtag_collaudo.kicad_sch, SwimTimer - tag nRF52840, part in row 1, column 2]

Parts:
C1, C5, C7, C12: 10u; C_0402_1005Metric; LCSC C15525
C2, C3, C4, C6, C8, C9: 100n; C_0402_1005Metric; LCSC C1525
C10, C11: 47u; C_0805_2012Metric; LCSC C16780
D1: 1N4148WS; D_SOD-323; LCSC C2128
D2: rosso; LED_0603_1608Metric; LCSC C2286
D3: SD05 TVS 5V; SOD-323_L1.8-W1.3-LS2.5-RD; LCSC C85201
D4: B5819WS; SOD-323_L1.8-W1.3-LS2.5-RD; LCSC C22624
J1: BATT JST-SH; JST_SH_SM02B-SRSS-TB_1x02-1MP_P1.00mm_Horizontal; LCSC C160402
J4: TC2030-NL; Tag-Connect_TC2030-IDC-NL_2x03_P1.27mm_Vertical
Q1, Q2: AO3400A; SOT-23; LCSC C20917
R1, R2, R5, R6, R9, R10: 10k; R_0402_1005Metric; LCSC C25744
R3: 100k; R_0402_1005Metric; LCSC C25741
R4: 1k; R_0402_1005Metric; LCSC C11702
R7, R8: 1M; R_0402_1005Metric; LCSC C26083
R11: 0; R_0402_1005Metric; LCSC C17168
TP1: VIN; TestPoint_Pad_D2.5mm
TP2: GND; TestPoint_Pad_D2.5mm
TP3: CHG_N; TestPoint_Pad_D0.8mm
TP4: SENS_ON; TestPoint_Pad_D0.8mm
TP5: VDD_SENS; TestPoint_Pad_D0.8mm
TP6: FG_ALRT; TestPoint_Pad_D0.8mm
TP7: VBAT; TestPoint_Pad_D1.0mm
TP8: VDD; TestPoint_Pad_D1.0mm
TP9: GND; TestPoint_Pad_D1.0mm
TP10: MOT+; TestPoint_Pad_1.0x1.0mm
TP11: MOT-; TestPoint_Pad_1.0x1.0mm
U1: E73-2G4M08S1C; WIRELM-SMD_E73-2G4M08S1C; LCSC C356849
U2: LSM6DSV16X; LGA-14_L3.0-W2.5-P0.50-BR; LCSC C5267406
U3: W25Q256JVEIQ; WSON-8_L8.0-W6.10-P1.27-BL-EP; LCSC C97522
U4: BQ25101; DSBGA-6_L0.9-W1.6-R2-C3-P0.40-BL; LCSC C478468
U5: MS5837-02BA; LGA-4_L3.3-W3.3-P2.00-TL; LCSC C5785272
U6: TPS22916C; DSBGA-4_L0.78-W0.78-P0.40; LCSC C2680319
U7: MAX17048; TDFN-8-1EP_2x2mm_P0.5mm_EP0.8x1.2mm; LCSC C2682616

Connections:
/BAT: C12.1, J1.1, R11.1, U4.A1 (OUT)
/CHG_N: TP3.1, U1.3 (P0.03/AIN1), U4.C1 (~CHG)
/FG_ALRT: TP6.1, U1.4 (P0.28/AIN4), U7.5 (ALRT)
/FG_SCL: R10.1, U1.35 (P0.24), U7.7 (SCL)
/FG_SDA: R9.1, U1.34 (P0.22), U7.8 (SDA)
/GND: C1.2, C2.2, C3.2, C4.2, C5.2, C6.2, C7.2, C9.2, C10.2, C11.2, C12.2, D3.2 (A), J1.2, J4.5 (GND), Q1.2 (S), Q2.2 (S), R1.2, R2.2, R3.2, R7.2, R8.2, TP2.1, TP9.1, U1.5 (GND), U1.21 (GND), U1.24 (GND), U2.2 (SDx/AH1/Qvar1), U2.3 (SCx/AH2/Qvar2), U2.6 (GND), U2.7 (GND), U3.4 (GND), U3.9 (EP), U4.C2 (VSS), U5.1 (GND), U6.B1 (GND), U7.1 (CTG), U7.4 (GND), U7.6 (QSTRT), U7.9 (EP)
/I2C_SCL: R6.1, U1.33 (P0.13), U5.3 (SCL)
/I2C_SDA: R5.1, U1.32 (P0.20), U5.4 (SDA)
/IMU_CS: U1.30 (P0.17), U2.12 (CS)
/IMU_INT1: U1.8 (P0.29/AIN5), U2.4 (INT1)
/IMU_INT2: U1.7 (P0.02/AIN0), U2.9 (INT2)
/IMU_MISO: U1.28 (P0.15), U2.1 (SDO/SA0)
/IMU_MOSI: U1.22 (P0.07), U2.14 (SDA)
/IMU_SCK: U1.20 (P0.12), U2.13 (SCL)
/ISET: R1.1, U4.B2 (ISET)
/LED: R4.2, U1.9 (P0.31/AIN7)
/LED_K: D2.1 (K), R4.1
/MOT_N: D1.2 (A), Q1.3 (D), TP11.1
/MOT_PWM: Q1.1 (G), R3.1, U1.10 (P0.30/AIN6)
/QSPI_CS: U1.12 (P0.26), U3.1 (~CS)
/QSPI_IO0: U1.18 (P0.04/AIN2), U3.5 (DI(IO0))
/QSPI_IO1: U1.14 (P0.06), U3.2 (DO(IO1))
/QSPI_IO2: U1.15 (P0.05/AIN3), U3.3 (WP#(IO2))
/QSPI_IO3: U1.16 (P0.08), U3.7 (HOLD#orRESET#(IO3))
/QSPI_SCK: U1.17 (P1.09), U3.6 (CLK)
/RESET: J4.3 (~RESET), Q2.3 (D), U1.26 (P0.18/RESET)
/RST_G: C8.2, Q2.1 (G), R7.1
/SENS_ON: R8.1, TP4.1, U1.6 (P1.13), U6.B2 (ON)
/SWDCLK: J4.4 (SWCLK), U1.39 (SWDCLK)
/SWDIO: J4.2 (SWDIO), U1.37 (SWDIO)
/TS: R2.1, U1.2 (P1.10), U4.B1 (TS)
/VBAT: C7.1, C9.1, C10.1, C11.1, D1.1 (K), D2.2 (A), R11.2, TP7.1, TP10.1, U1.23 (VDDH), U7.2 (CELL), U7.3 (VDD)
/VDD: C1.1, C3.1, J4.1 (VCC), R9.2, R10.2, TP8.1, U1.19 (VDD), U3.8 (VCC), U6.A2 (VIN)
/VDD_SENS: C2.1, C4.1, C6.1, R5.2, R6.2, TP5.1, U2.5 (Vdd_IO), U2.8 (Vdd), U5.2 (VDD), U6.A1 (VOUT)
/VIN: D3.1 (C), D4.2 (A), TP1.1
/VIN_D: C5.1, C8.1, D4.1 (K), U1.27 (VBUS), U4.A2 (IN)

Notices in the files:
README.md:
License and author:
Project license: to be defined (no `LICENSE` file). The driver in `firmware/display-prova/src/trgb/` is under the MIT license (Copyright 2024 Xinyuan-LilyGO), with its own `LICENSE` file.
Author: PZero (GitHub `PZero`).
- **Live**: 3D orientation of the tag from the IMU, battery card, head-mounting calibration (*Calibra*, *Ricentra*), charts of the accelerometer and gyroscope. The head model is the Lee Perry-Smith 3D scan (Infinite-Realities), licensed CC BY 3.0, loaded from a public CDN.
